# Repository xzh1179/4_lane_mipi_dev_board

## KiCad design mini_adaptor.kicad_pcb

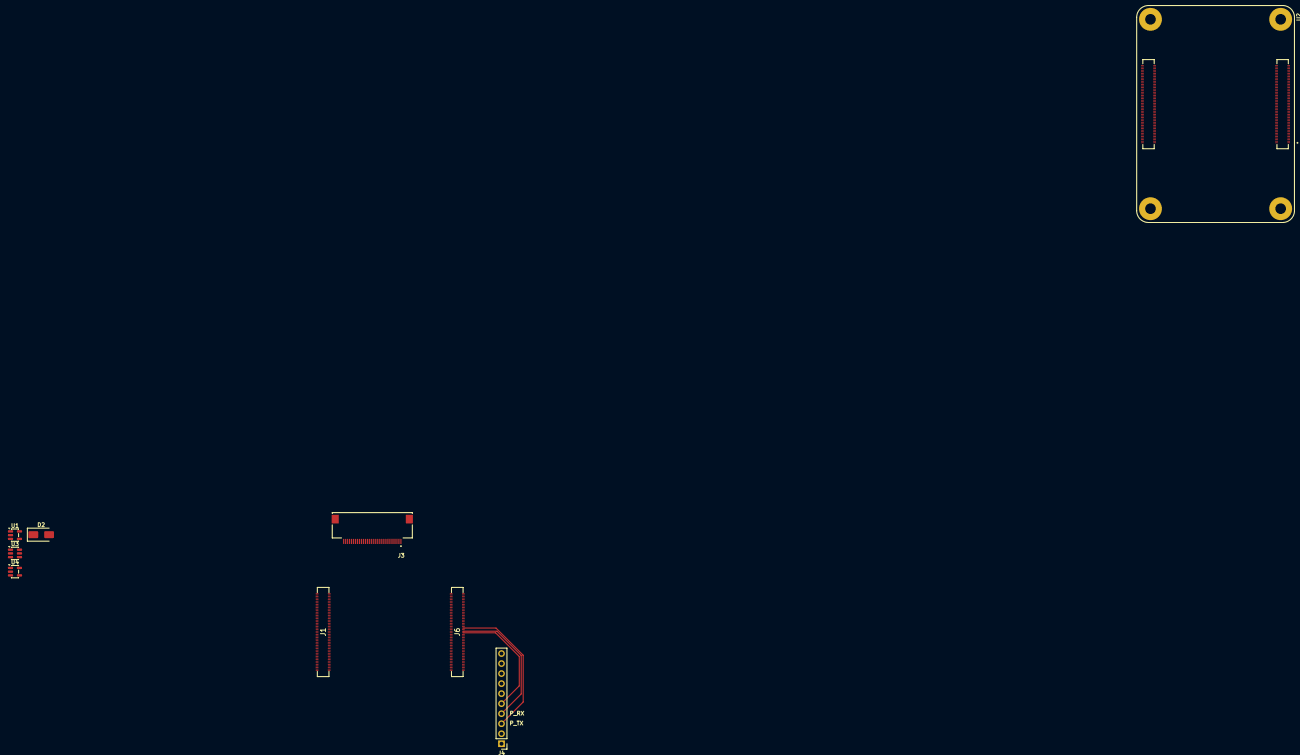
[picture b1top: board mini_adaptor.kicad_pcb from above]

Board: 2 copper layers, 9 parts (0 on the bottom side), 24 nets.

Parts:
D2: SMAJ6.0A; D_SMA
J1, J6: DF40HC_3.0_-100DS-0.4V_51; DF40HC30100DS04V51
J3: Conn_01x30_Pin; AMPHENOL_F31L-1A7H1-11030
J4: Conn_01x10_Pin; PinHeader_1x10_P2.54mm_Vertical
U1, U4: TLV62568DBV; SOT-23-5
U2: CM4102008; MODULE_CM4102008
U3: TPS61165DBV; SOT-23-6

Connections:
+5V(INPUT): U2.77 (+5V(INPUT)), U2.79 (+5V(INPUT)), U2.81 (+5V(INPUT)), U2.83 (+5V(INPUT)), U2.85 (+5V(INPUT)), U2.87 (+5V(INPUT))
/CM4_1V8: J6.88, J6.90
/CM4_3V3: J6.84, J6.86
/CM4_5V: J4.1, J6.77, J6.79, J6.81, J6.83, J6.85, J6.87
/DSI1_CLK_N: J1.87, J3.13
/DSI1_CLK_P: J1.89, J3.14
/DSI1_D0_N: J1.75, J3.7
/DSI1_D0_P: J1.77, J3.8
/DSI1_D1_N: J1.81, J3.10
/DSI1_D1_P: J1.83, J3.11
/DSI1_D2_N: J1.93, J3.16
/DSI1_D2_P: J1.95, J3.17
/DSI1_D3_N: J1.94, J3.19
/DSI1_D3_P: J1.96, J3.20
/GPIO14: J4.3, J6.55
/GPIO15: J4.4, J6.51
/GPIO18: J4.5, J6.49
/LEDA: J3.3, J3.4
/LEDK: J3.1, J3.2, U3.6 (FB)
CM4_1.8V(OUTPUT): U2.88 (CM4_1.8V(OUTPUT)), U2.90 (CM4_1.8V(OUTPUT))
CM4_3.3V(OUTPUT): U2.84 (CM4_3.3V(OUTPUT)), U2.86 (CM4_3.3V(OUTPUT))
GND: D2.2 (A2), J1.7, J1.8, J1.13, J1.14, J1.19, J1.20, J1.25, J1.26, J1.31, J1.32, J1.37, J1.38, J1.44, J1.50, J1.55, J1.56, J1.61, J1.62, J1.67, J1.68, J1.73, J1.74, J1.79, J1.80, J1.85, J1.86, J1.91, J1.92, J1.97, J1.98, J3.6, J3.9, J3.12, J3.15, J3.18, J3.21, J3.22, J3.24, J3.29, J3.30, J6.1, J6.2, J6.7, J6.8, J6.13, J6.14, J6.19, J6.22, J6.23, J6.32, J6.33, J6.42, J6.43, J6.52, J6.53, J6.59, J6.60, J6.65, J6.66, J6.71, J6.74, J6.98, U1.2 (GND), U2.1 (GND), U2.2 (GND), U2.7 (GND), U2.8 (GND), U2.13 (GND), U2.14 (GND), U2.22 (GND), U2.23 (GND), U2.32 (GND), U2.33 (GND), U2.42 (GND), U2.43 (GND), U2.52 (GND), U2.53 (GND), U2.59 (GND), U2.60 (GND), U2.65 (GND), U2.66 (GND), U2.71 (GND), U2.74 (GND), U2.98 (GND), U2.107 (GND), U2.108 (GND), U2.113 (GND), U2.114 (GND), U2.119 (GND), U2.120 (GND), U2.125 (GND), U2.126 (GND), U2.131 (GND), U2.132 (GND), U2.137 (GND), U2.138 (GND), U2.144 (GND), U2.150 (GND), U2.155 (GND), U2.156 (GND), U2.161 (GND), U2.162 (GND), U2.167 (GND), U2.168 (GND), U2.173 (GND), U2.174 (GND), U2.179 (GND), U2.180 (GND), U2.185 (GND), U2.186 (GND), U2.191 (GND), U2.192 (GND), U2.197 (GND), U2.198 (GND), U3.4 (GND), U4.2 (GND)
unnamed: U2.SH1 (MOUNTING_PADS), U2.SH2 (MOUNTING_PADS), U2.SH3 (MOUNTING_PADS), U2.SH4 (MOUNTING_PADS)
VUSB: D2.1 (A1), U1.1 (EN), U1.4 (VIN), U3.1 (VIN), U4.1 (EN), U4.4 (VIN)

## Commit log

2026-06-02 feat: routing ongoing
